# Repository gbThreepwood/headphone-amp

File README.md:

# Headphone amplifier

A headphone amplifier project consisting of the following parts:

* Amplifier PCB
* Amplifier front panel PCB
* Power supply PCB
* Annotated aluminium front panels
* 3D model of full assembly

## Power supply

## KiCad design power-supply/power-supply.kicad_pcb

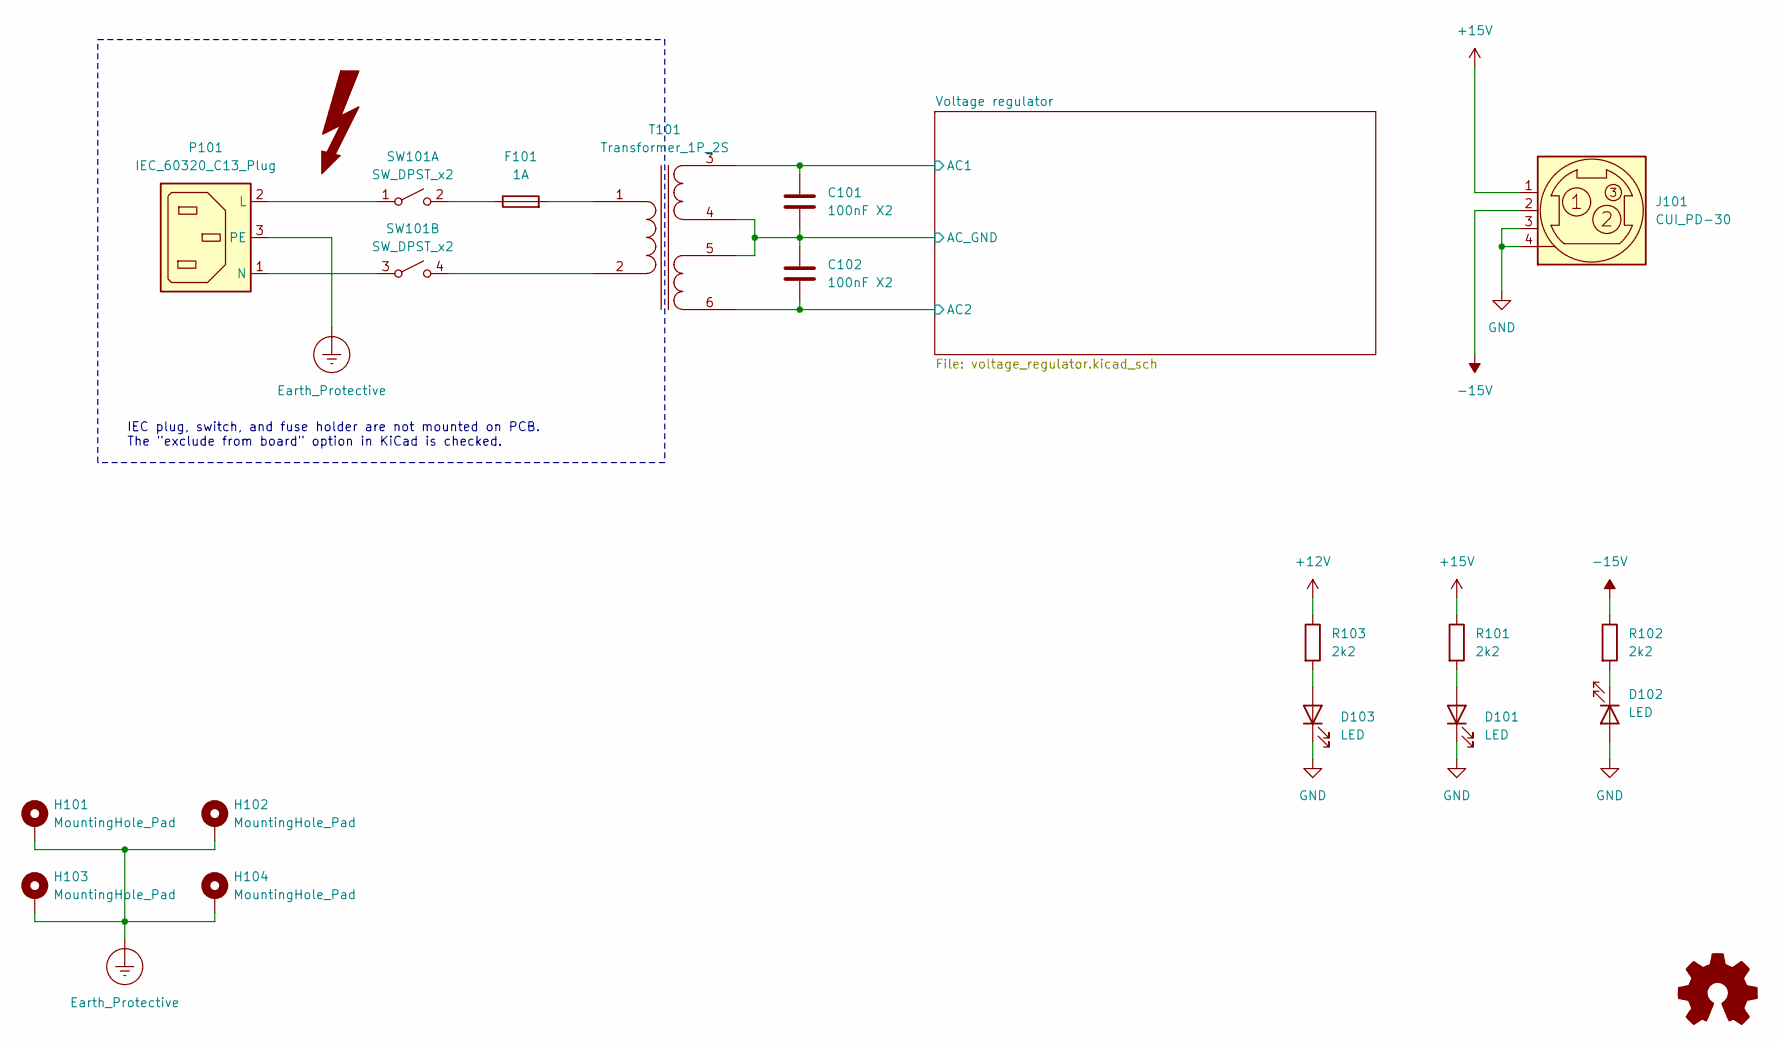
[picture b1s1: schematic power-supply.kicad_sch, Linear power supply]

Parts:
C101, C102: 100nF X2; C_Axial_L19.0mm_D7.5mm_P25.00mm_Horizontal
D101, D102, D103: LED; LED_D5.0mm_Horizontal_O3.81mm_Z3.0mm
F101: 1A
H101, H102, H103, H104: MountingHole_Pad; MountingHole_4mm_Pad_TopBottom
J101: CUI_PD-30
P101: IEC_60320_C13_Plug
R101, R102, R103: 2k2; R_Axial_DIN0207_L6.3mm_D2.5mm_P10.16mm_Horizontal
SW101: SW_DPST_x2
T101: Transformer_1P_2S; ToroidalTransformer 30VA

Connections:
+12V: R103.1; also elsewhere on the board
+15V: J101.1, R101.1; also elsewhere on the board
-15V: J101.2, R102.1; also elsewhere on the board
/Voltage regulator/AC1: C101.1, T101.3 (SA); also elsewhere on the board
/Voltage regulator/AC2: C102.2, T101.6 (SD); also elsewhere on the board
Earth_Protective: H101.1, H102.1, H103.1, H104.1, P101.3 (PE)
GND: C101.2, C102.1, D101.1 (K), D102.2 (A), D103.1 (K), J101.3, J101.4 (Shield), T101.4 (SB), T101.5 (SC); also elsewhere on the board
unnamed: D101.2 (A), R101.2
unnamed: D102.1 (K), R102.2
unnamed: D103.2 (A), R103.2
unnamed: F101.1, SW101.2 (B)
unnamed: P101.1 (N), SW101.3 (A)
unnamed: P101.2 (L), SW101.1 (A)
unnamed: F101.2, T101.1 (AA)
unnamed: SW101.4 (B), T101.2 (AB)

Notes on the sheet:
IEC plug, switch, and fuse holder are not mounted on PCB. The "exclude from board" option in KiCad is checked.

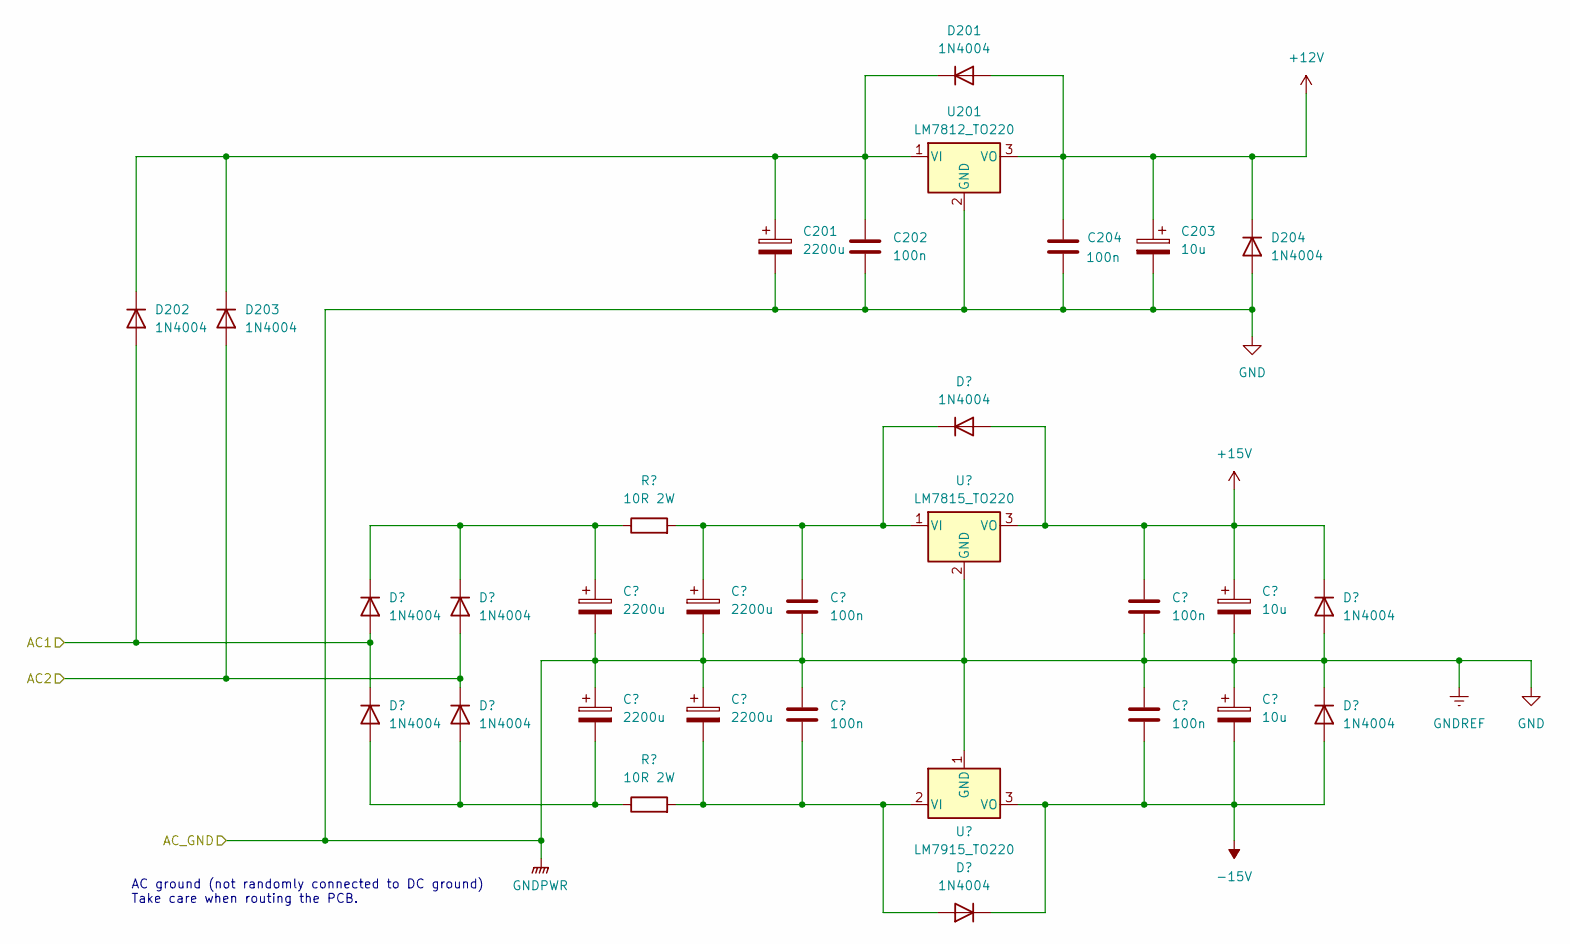
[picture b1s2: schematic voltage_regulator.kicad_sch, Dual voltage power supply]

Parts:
C201, C401, C402, C403, C404: 2200u; CP_Radial_D18.0mm_P7.50mm
C202, C204, C405, C406, C407, C408: 100n; C_Disc_D6.0mm_W2.5mm_P5.00mm
C203, C409, C410: 10u; CP_Radial_D5.0mm_P2.00mm
D201, D202, D203, D204, D401, D402, D403, D404, D405, D406, D408, D409: 1N4004; D_DO-41_SOD81_P10.16mm_Horizontal
R401, R402: 10R 2W; R_Axial_DIN0309_L9.0mm_D3.2mm_P12.70mm_Horizontal
U201: LM7812_TO220; TO-220-3_Vertical
U401: LM7815_TO220; TO-220-3_Vertical
U402: LM7915_TO220; TO-220-3_Vertical

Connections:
+12V: C203.1, C204.1, D201.2 (A), D204.1 (K), U201.3 (VO); also elsewhere on the board
+15V: C407.1, C409.1, D405.2 (A), D408.1 (K), U401.3 (VO); also elsewhere on the board
-15V: C408.2, C410.2, D406.1 (K), D409.2 (A), U402.3 (VO); also elsewhere on the board
/Voltage regulator/AC1: D202.2 (A), D401.2 (A), D402.1 (K); also elsewhere on the board
/Voltage regulator/AC2: D203.2 (A), D403.2 (A), D404.1 (K); also elsewhere on the board
GND: C201.2, C202.2, C203.2, C204.2, C401.2, C402.1, C403.2, C404.1, C405.2, C406.1, C407.2, C408.1, C409.2, C410.1, D204.2 (A), D408.2 (A), D409.1 (K), U201.2 (GND), U401.2 (GND), U402.1 (GND); also elsewhere on the board
unnamed: C201.1, C202.1, D201.1 (K), D202.1 (K), D203.1 (K), U201.1 (VI)
unnamed: C401.1, D401.1 (K), D403.1 (K), R401.1
unnamed: C402.2, D402.2 (A), D404.2 (A), R402.1
unnamed: C403.1, C405.1, D405.1 (K), R401.2, U401.1 (VI)
unnamed: C404.2, C406.2, D406.2 (A), R402.2, U402.2 (VI)

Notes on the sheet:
AC ground (not randomly connected to DC ground) Take care when routing the PCB.

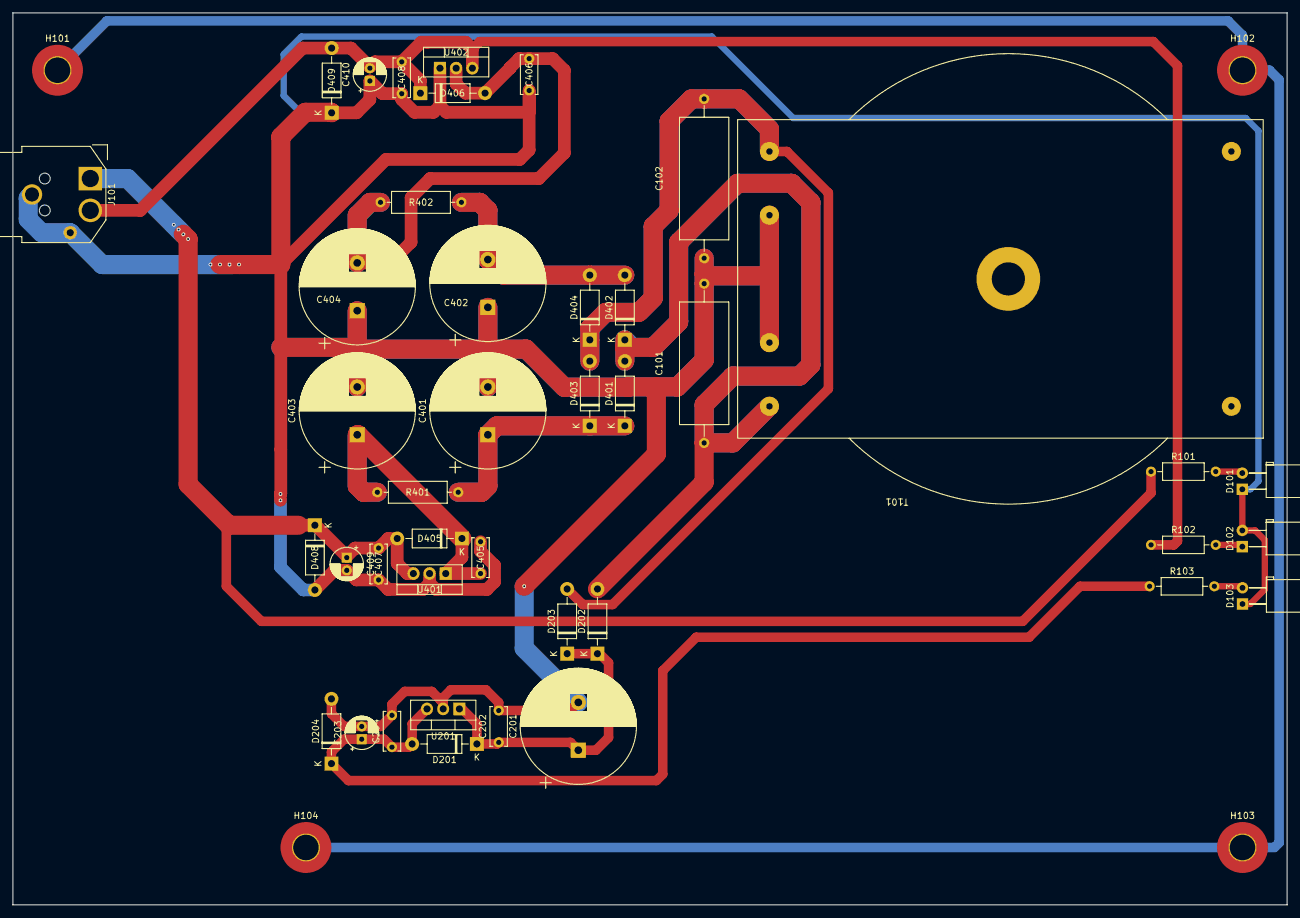
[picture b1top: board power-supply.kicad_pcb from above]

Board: 2 copper layers, 200.0 x 140.0 mm, 45 parts (0 on the bottom side), 15 nets.

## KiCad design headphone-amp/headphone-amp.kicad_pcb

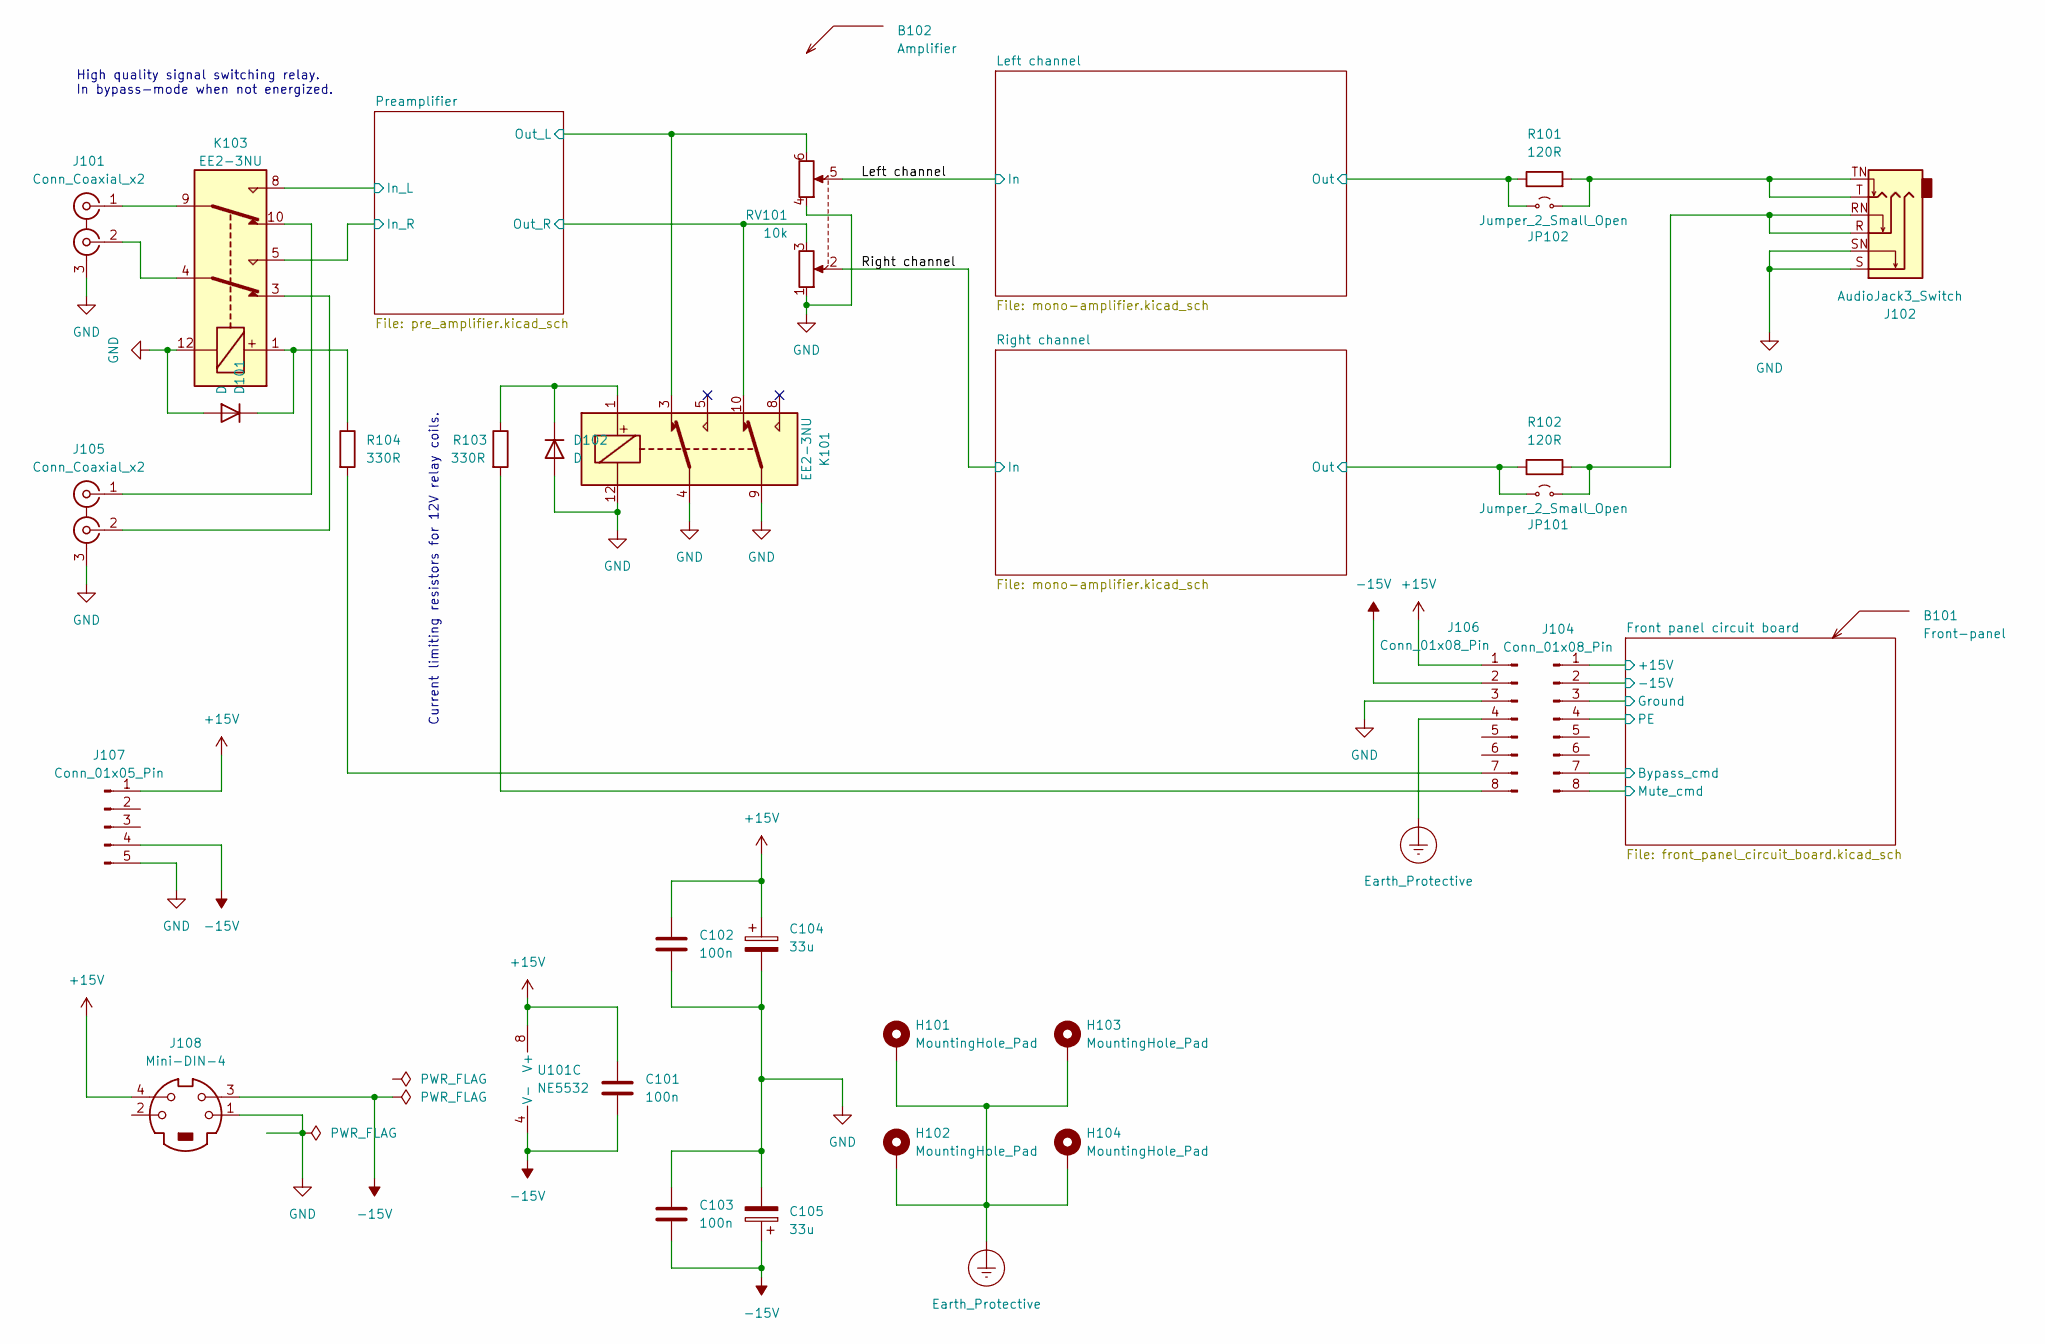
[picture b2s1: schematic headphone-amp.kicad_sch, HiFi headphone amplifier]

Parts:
B101: Front-panel; Board
B102: Amplifier; Board
C101, C102, C103: 100n; C_Disc_D6.0mm_W2.5mm_P5.00mm
C104, C105: 33u; CP_Radial_D6.3mm_P2.50mm
D101, D102: D; D_DO-35_SOD27_P7.62mm_Horizontal
H101, H102, H103, H104: MountingHole_Pad; MountingHole_4.3mm_M4_DIN965_Pad_TopBottom
J101, J105: Conn_Coaxial_x2; rcj-22 vertical RCA
J102: AudioJack3_Switch; CUI_SJ-63073E
J104, J106: Conn_01x08_Pin; PinHeader_1x08_P2.54mm_Vertical
J107: Conn_01x05_Pin; PhoenixContact_GMSTB_2,5_5-GF-7,62_1x05_P7.62mm_Horizontal_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
J108: Mini-DIN-4
JP101, JP102: Jumper_2_Small_Open; PinHeader_2x01_P2.54mm_Vertical
K101, K103: EE2-3NU; Relay_DPDT_Kemet_EE2_NU
R101, R102: 120R; R_Axial_DIN0207_L6.3mm_D2.5mm_P10.16mm_Horizontal
R103, R104: 330R; R_Axial_DIN0207_L6.3mm_D2.5mm_P10.16mm_Horizontal
RV101: 10k; Potentiometer_Alps_RK163_Dual_Horizontal
U101: NE5532; DIP-8_W7.62mm_LongPads

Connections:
+15V: C101.1, C102.1, C104.1, J106.1, J107.1, J108.4, U101.8 (V+); also elsewhere on the board
-15V: C101.2, C103.1, C105.1, J106.2, J107.4, J108.3, U101.4 (V-); also elsewhere on the board
/Front panel circuit board/+15V: J104.1; also elsewhere on the board
/Front panel circuit board/-15V: J104.2
/Front panel circuit board/Bypass_cmd: J104.7; also elsewhere on the board
/Front panel circuit board/Ground: J104.3; also elsewhere on the board
/Front panel circuit board/Mute_cmd: J104.8; also elsewhere on the board
/Front panel circuit board/PE: J104.4; also elsewhere on the board
/Left channel: RV101.5; also elsewhere on the board
/Left channel/Out: JP102.1 (A), R101.1; also elsewhere on the board
/Preamplifier/In_L: K103.8; also elsewhere on the board
/Preamplifier/In_R: K103.5; also elsewhere on the board
/Preamplifier/Out_L: K101.3, RV101.6; also elsewhere on the board
/Preamplifier/Out_R: K101.10, RV101.3; also elsewhere on the board
/Right channel: RV101.2; also elsewhere on the board
/Right channel/Out: JP101.1 (A), R102.1; also elsewhere on the board
Earth_Protective: H101.1, H102.1, H103.1, H104.1, J106.4
GND: C102.2, C103.2, C104.2, C105.2, D101.2 (A), D102.2 (A), J101.3 (EXT), J102.S, J102.SN, J105.3 (EXT), J106.3, J107.5, J108.1, K101.4, K101.9, K101.12, K103.12, RV101.1, RV101.4; also elsewhere on the board
unnamed: D101.1 (K), K103.1, R104.1
unnamed: D102.1 (K), K101.1, R103.1
unnamed 31: U101.1; also elsewhere on the board
unnamed: J101.1 (IN1), K103.9
unnamed: J101.2 (IN2), K103.4
unnamed: J105.1 (IN1), K103.10
unnamed: J105.2 (IN2), K103.3
unnamed: J106.7, R104.2
unnamed: J106.8, R103.2
unnamed: J102.R, J102.RN, JP101.2 (B), R102.2
unnamed: J102.T, J102.TN, JP102.2 (B), R101.2
unnamed 55: U101.3 (+); also elsewhere on the board
unnamed 56: U101.2 (-); also elsewhere on the board

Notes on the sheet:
Current limiting resistors for 12V relay coils.
High quality signal switching relay. In bypass-mode when not energized.

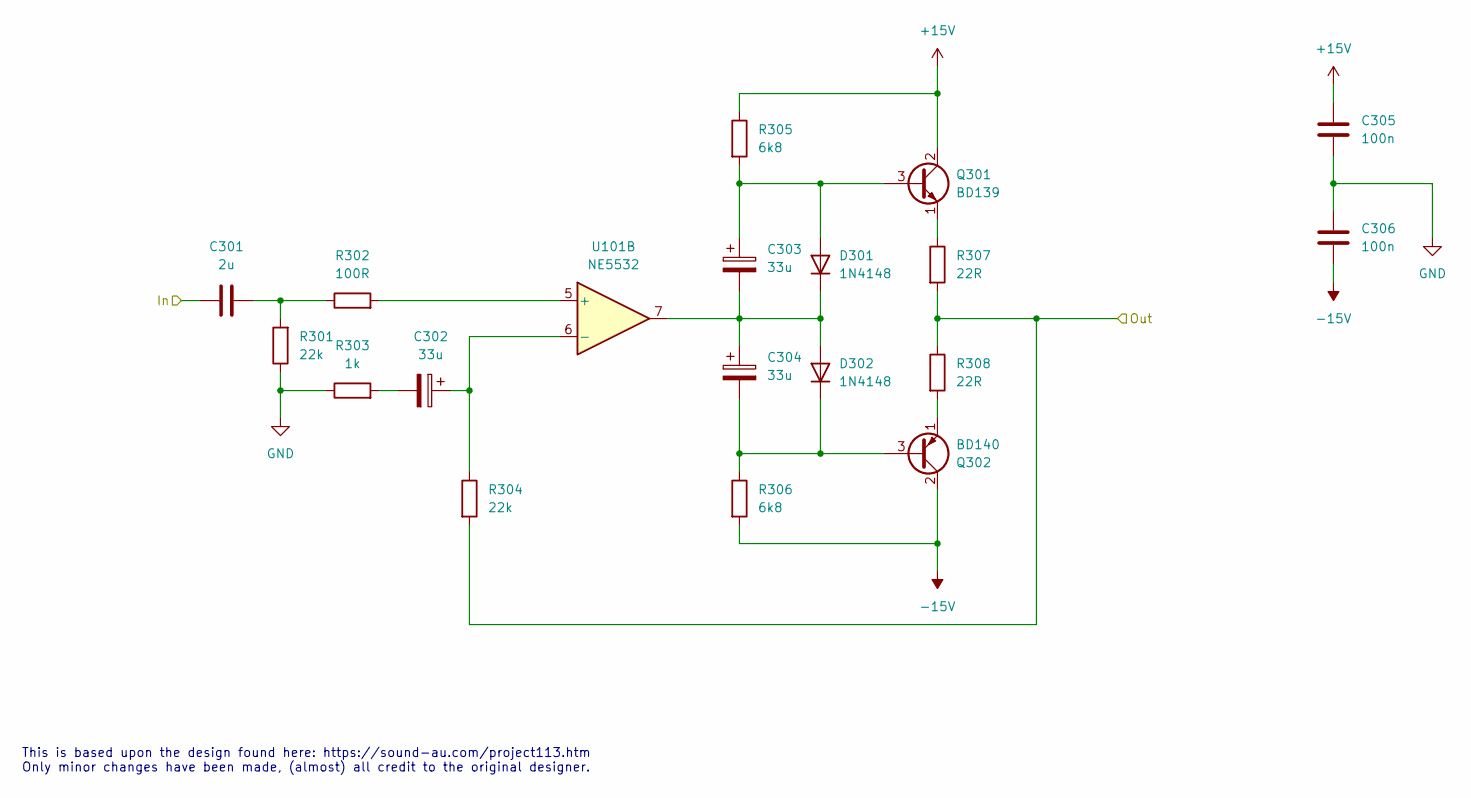
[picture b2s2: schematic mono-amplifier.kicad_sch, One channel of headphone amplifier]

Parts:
C301: 2u; C_Axial_L12.0mm_D7.5mm_P15.00mm_Horizontal
C302, C303, C304: 33u; CP_Radial_D6.3mm_P2.50mm
C305, C306: 100n; C_Disc_D6.0mm_W2.5mm_P5.00mm
D301, D302: 1N4148; D_DO-35_SOD27_P7.62mm_Horizontal
Q301: BD139; TO-126-3_Vertical
Q302: BD140; TO-126-3_Vertical
R301, R304: 22k; R_Axial_DIN0207_L6.3mm_D2.5mm_P10.16mm_Horizontal
R302: 100R; R_Axial_DIN0207_L6.3mm_D2.5mm_P10.16mm_Horizontal
R303: 1k; R_Axial_DIN0207_L6.3mm_D2.5mm_P10.16mm_Horizontal
R305, R306: 6k8; R_Axial_DIN0207_L6.3mm_D2.5mm_P10.16mm_Horizontal
R307, R308: 22R; R_Axial_DIN0207_L6.3mm_D2.5mm_P10.16mm_Horizontal
U101: NE5532; DIP-8_W7.62mm_LongPads

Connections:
+15V: C305.2, Q301.2 (C), R305.1; also elsewhere on the board
-15V: C306.1, Q302.2 (C), R306.2; also elsewhere on the board
/Right channel: C301.1; also elsewhere on the board
/Right channel/Out: R304.2, R307.2, R308.1; also elsewhere on the board
GND: C305.1, C306.2, R301.1, R303.1; also elsewhere on the board
unnamed: C301.2, R301.2, R302.1
unnamed: C302.2, R303.2
unnamed 31: U101.1; also elsewhere on the board
unnamed: C303.1, D301.2 (A), Q301.3 (B), R305.2
unnamed: C303.2, C304.1, D301.1 (K), D302.2 (A), U101.7
unnamed: C304.2, D302.1 (K), Q302.3 (B), R306.1
unnamed: Q301.1 (E), R307.1
unnamed: Q302.1 (E), R308.2
unnamed 55: U101.3 (+); also elsewhere on the board
unnamed 56: U101.2 (-); also elsewhere on the board
unnamed: R302.2, U101.5 (+)
unnamed: C302.1, R304.1, U101.6 (-)

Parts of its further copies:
C201: 2u; C_Axial_L12.0mm_D7.5mm_P15.00mm_Horizontal
C202, C203, C204: 33u; CP_Radial_D6.3mm_P2.50mm
C205, C206: 100n; C_Disc_D6.0mm_W2.5mm_P5.00mm
D201, D202: 1N4148; D_DO-35_SOD27_P7.62mm_Horizontal
Q201: BD139; TO-126-3_Vertical
Q202: BD140; TO-126-3_Vertical
R201, R204: 22k; R_Axial_DIN0207_L6.3mm_D2.5mm_P10.16mm_Horizontal
R202: 100R; R_Axial_DIN0207_L6.3mm_D2.5mm_P10.16mm_Horizontal
R203: 1k; R_Axial_DIN0207_L6.3mm_D2.5mm_P10.16mm_Horizontal
R205, R206: 6k8; R_Axial_DIN0207_L6.3mm_D2.5mm_P10.16mm_Horizontal
R207, R208: 22R; R_Axial_DIN0207_L6.3mm_D2.5mm_P10.16mm_Horizontal

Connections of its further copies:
+15V: C205.2, Q201.2 (C), R205.1; also elsewhere on the board
-15V: C206.1, Q202.2 (C), R206.2; also elsewhere on the board
/Left channel: C201.1; also elsewhere on the board
/Left channel/Out: R204.2, R207.2, R208.1; also elsewhere on the board
GND: C205.1, C206.2, R201.1, R203.1; also elsewhere on the board
unnamed: C201.2, R201.2, R202.1
unnamed: C202.2, R203.2
unnamed: C203.1, D201.2 (A), Q201.3 (B), R205.2
unnamed 31: C203.2, C204.1, D201.1 (K), D202.2 (A); also elsewhere on the board
unnamed: C204.2, D202.1 (K), Q202.3 (B), R206.1
unnamed: Q201.1 (E), R207.1
unnamed: Q202.1 (E), R208.2
unnamed 55: R202.2; also elsewhere on the board
unnamed 56: C202.1, R204.1; also elsewhere on the board

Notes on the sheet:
This is based upon the design found here: https://sound-au.com/project113.htm Only minor changes have been made, (almost) all credit to the original designer.

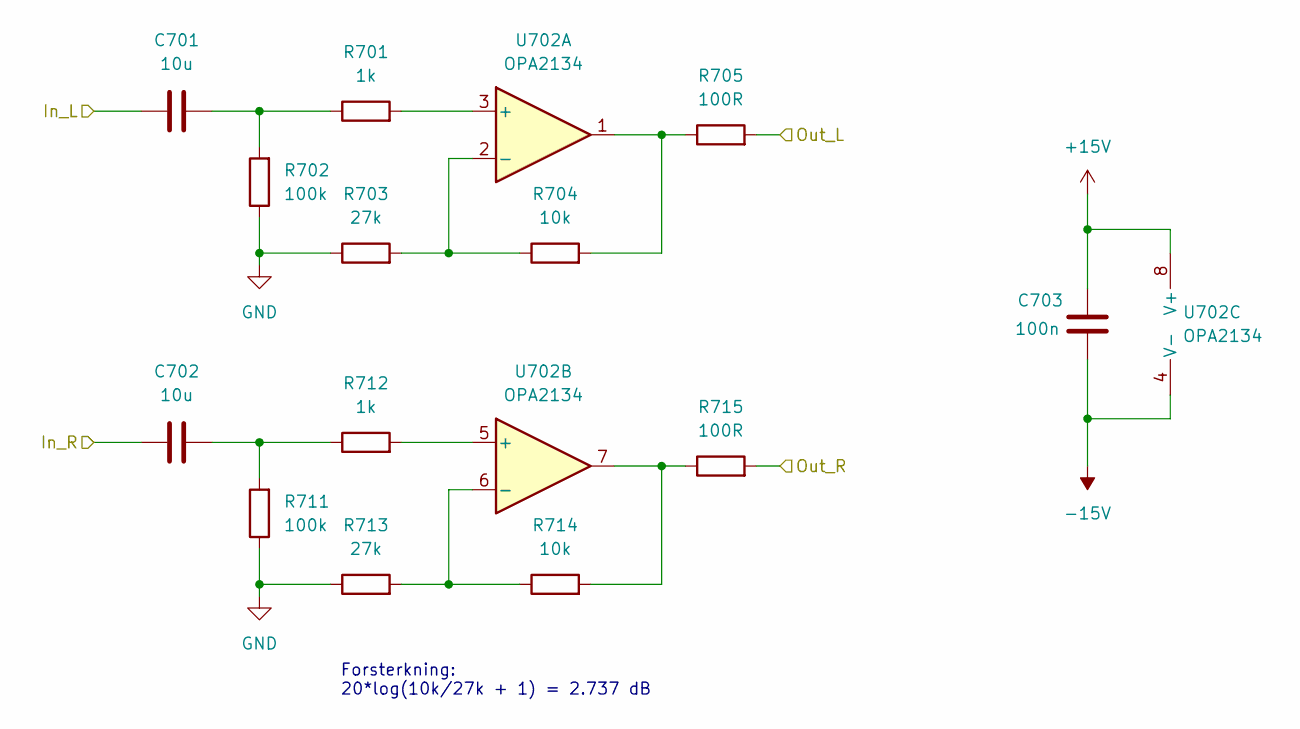
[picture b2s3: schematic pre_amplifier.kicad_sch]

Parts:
C701, C702: 10u; C_Axial_L12.0mm_D7.5mm_P15.00mm_Horizontal
C703: 100n; C_Disc_D6.0mm_W2.5mm_P5.00mm
R701, R712: 1k; R_Axial_DIN0207_L6.3mm_D2.5mm_P10.16mm_Horizontal
R702, R711: 100k; R_Axial_DIN0207_L6.3mm_D2.5mm_P10.16mm_Horizontal
R703, R713: 27k; R_Axial_DIN0207_L6.3mm_D2.5mm_P10.16mm_Horizontal
R704, R714: 10k; R_Axial_DIN0207_L6.3mm_D2.5mm_P10.16mm_Horizontal
R705, R715: 100R; R_Axial_DIN0207_L6.3mm_D2.5mm_P10.16mm_Horizontal
U702: OPA2134; DIP-8_W7.62mm_LongPads

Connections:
+15V: C703.1, U702.8 (V+); also elsewhere on the board
-15V: C703.2, U702.4 (V-); also elsewhere on the board
/Preamplifier/In_L: C701.1; also elsewhere on the board
/Preamplifier/In_R: C702.1; also elsewhere on the board
/Preamplifier/Out_L: R705.2; also elsewhere on the board
/Preamplifier/Out_R: R715.2; also elsewhere on the board
GND: R702.1, R703.1, R711.1, R713.1; also elsewhere on the board
unnamed: C701.2, R701.1, R702.2
unnamed: C702.2, R711.2, R712.1
unnamed: R704.2, R705.1, U702.1
unnamed: R714.2, R715.1, U702.7
unnamed: R701.2, U702.3 (+)
unnamed: R703.2, R704.1, U702.2 (-)
unnamed: R712.2, U702.5 (+)
unnamed: R713.2, R714.1, U702.6 (-)

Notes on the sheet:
Forsterkning: 20*log(10k/27k + 1) = 2.737 dB

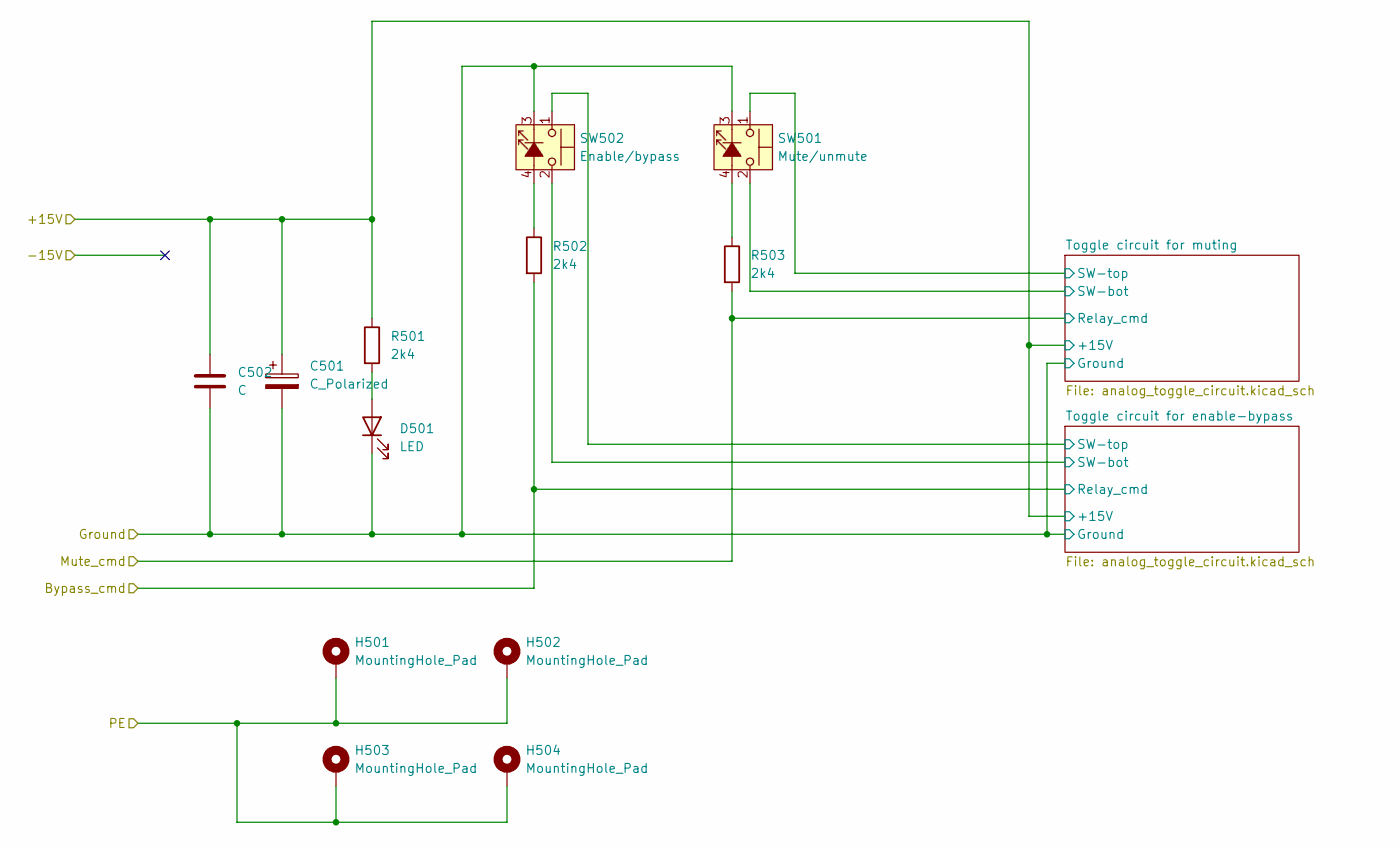
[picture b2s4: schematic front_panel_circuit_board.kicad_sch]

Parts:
C501: C_Polarized; CP_Elec_6.3x5.8
C502: C; C_1206_3216Metric_Pad1.33x1.80mm_HandSolder
D501: LED; LED_1812_4532Metric
H501, H502, H503, H504: MountingHole_Pad; MountingHole_4.3mm_M4_DIN965_Pad_TopBottom
R501, R502, R503: 2k4; R_1206_3216Metric_Pad1.30x1.75mm_HandSolder
SW501: Mute/unmute; SW_Push_2P1T_Toggle_CK_PVA1xxH1xxxxxxV2
SW502: Enable/bypass; SW_Push_2P1T_Toggle_CK_PVA1xxH1xxxxxxV2

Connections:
/Front panel circuit board/+15V: C501.1, C502.1, R501.1; also elsewhere on the board
/Front panel circuit board/Bypass_cmd: R502.2; also elsewhere on the board
/Front panel circuit board/Ground: C501.2, C502.2, D501.1 (K), SW501.3 (K), SW502.3 (K); also elsewhere on the board
/Front panel circuit board/Mute_cmd: R503.2; also elsewhere on the board
/Front panel circuit board/PE: H501.1, H502.1, H503.1, H504.1; also elsewhere on the board
/Front panel circuit board/Toggle circuit for enable-bypass/SW-bot: SW502.2; also elsewhere on the board
/Front panel circuit board/Toggle circuit for enable-bypass/SW-top: SW502.1; also elsewhere on the board
/Front panel circuit board/Toggle circuit for muting/SW-bot: SW501.2; also elsewhere on the board
/Front panel circuit board/Toggle circuit for muting/SW-top: SW501.1; also elsewhere on the board
unnamed: D501.2 (A), R501.2
unnamed: R503.1, SW501.4 (A)
unnamed: R502.1, SW502.4 (A)

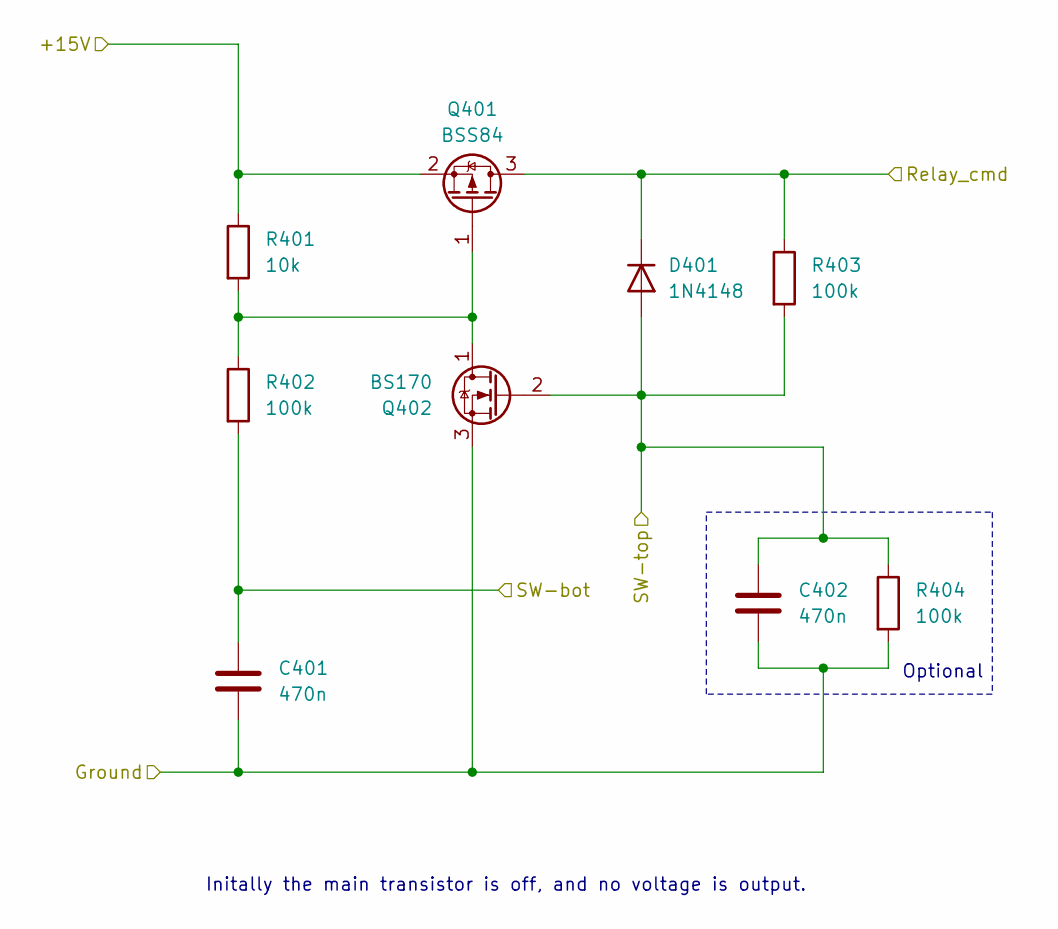
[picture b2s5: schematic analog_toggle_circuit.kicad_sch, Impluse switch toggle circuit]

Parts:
C401, C402: 470n; C_1206_3216Metric_Pad1.33x1.80mm_HandSolder
D401: 1N4148; D_SOD-123
Q401: BSS84; SOT-23
Q402: BS170; SOT-23
R401: 10k; R_1206_3216Metric_Pad1.30x1.75mm_HandSolder
R402, R403, R404: 100k; R_1206_3216Metric_Pad1.30x1.75mm_HandSolder

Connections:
/Front panel circuit board/+15V: Q401.2 (S), R401.1; also elsewhere on the board
/Front panel circuit board/Ground: C401.2, C402.2, Q402.3 (S), R404.2; also elsewhere on the board
/Front panel circuit board/Mute_cmd: D401.1 (K), Q401.3 (D), R403.1; also elsewhere on the board
/Front panel circuit board/Toggle circuit for muting/SW-bot: C401.1, R402.2; also elsewhere on the board
/Front panel circuit board/Toggle circuit for muting/SW-top: C402.1, D401.2 (A), Q402.2 (G), R403.2, R404.1; also elsewhere on the board
unnamed: Q401.1 (G), Q402.1 (D), R401.2, R402.1

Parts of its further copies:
C601, C602: 470n; C_1206_3216Metric_Pad1.33x1.80mm_HandSolder
D601: 1N4148; D_SOD-123
Q601: BSS84; SOT-23
Q602: BS170; SOT-23
R601: 10k; R_1206_3216Metric_Pad1.30x1.75mm_HandSolder
R602, R603, R604: 100k; R_1206_3216Metric_Pad1.30x1.75mm_HandSolder

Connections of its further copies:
/Front panel circuit board/+15V: Q601.2 (S), R601.1; also elsewhere on the board
/Front panel circuit board/Bypass_cmd: D601.1 (K), Q601.3 (D), R603.1; also elsewhere on the board
/Front panel circuit board/Ground: C601.2, C602.2, Q602.3 (S), R604.2; also elsewhere on the board
/Front panel circuit board/Toggle circuit for enable-bypass/SW-bot: C601.1, R602.2; also elsewhere on the board
/Front panel circuit board/Toggle circuit for enable-bypass/SW-top: C602.1, D601.2 (A), Q602.2 (G), R603.2, R604.1; also elsewhere on the board
unnamed: Q601.1 (G), Q602.1 (D), R601.2, R602.1

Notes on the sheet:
Initally the main transistor is off, and no voltage is output.
Optional

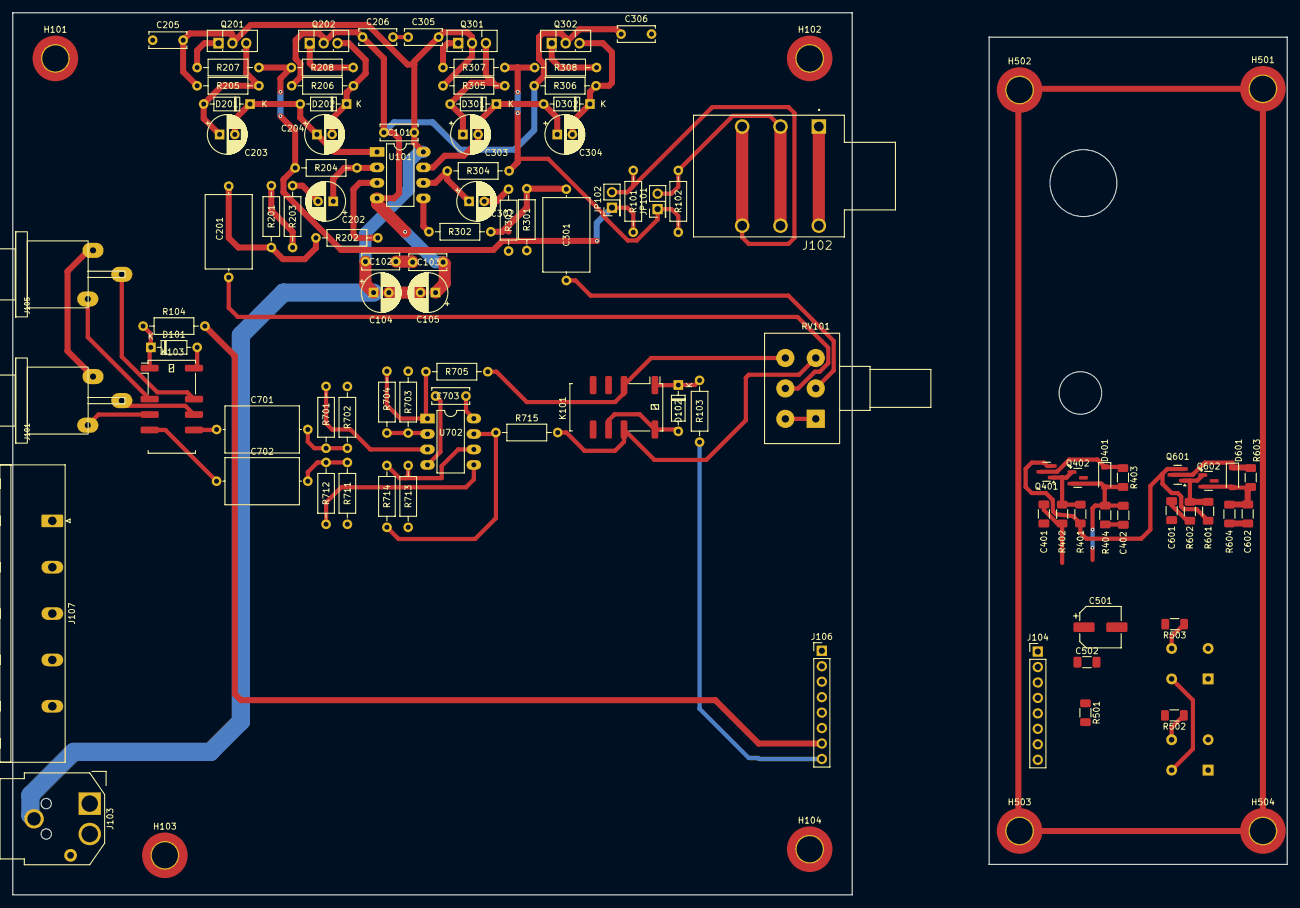
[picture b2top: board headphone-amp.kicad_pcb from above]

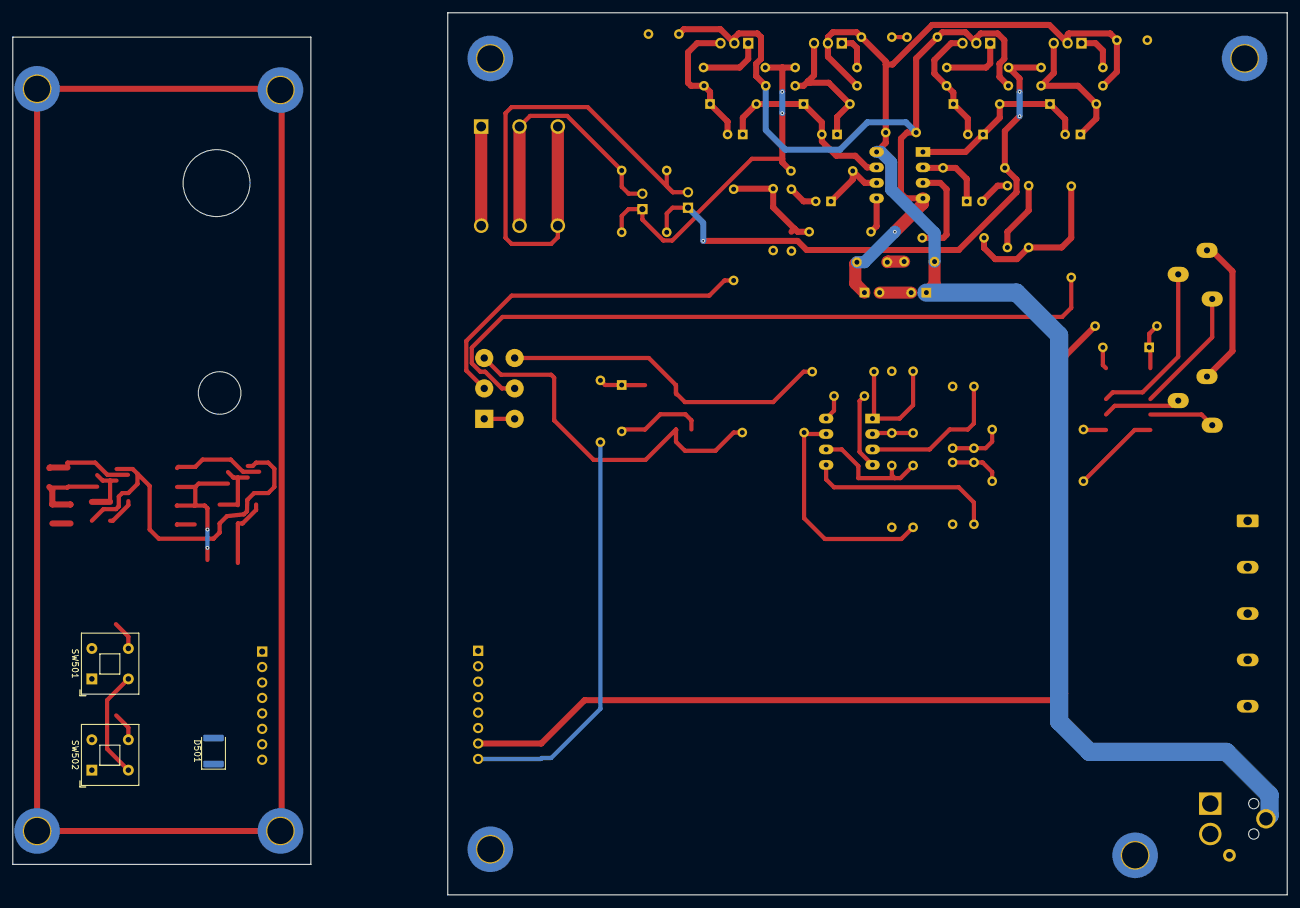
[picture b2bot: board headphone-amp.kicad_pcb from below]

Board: 2 copper layers, 209.5 x 145.0 mm, 110 parts (3 on the bottom side), 62 nets.

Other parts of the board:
J103: CUI_PD-30

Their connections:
+15V: J103.4 (Shield); also elsewhere on the board
-15V: J103.3; also elsewhere on the board
GND: J103.1, J103.2; also elsewhere on the board

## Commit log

2024-12-26 Added 3d-model of power supply enclosure
2024-12-26 Added picture
2025-01-01 Added simulation of toggle switch circuit
2025-01-01 Added .gitignore for FreeCAD
2025-01-01 Updated headphone-amp kicad project
2025-01-01 Some additions to power supply
